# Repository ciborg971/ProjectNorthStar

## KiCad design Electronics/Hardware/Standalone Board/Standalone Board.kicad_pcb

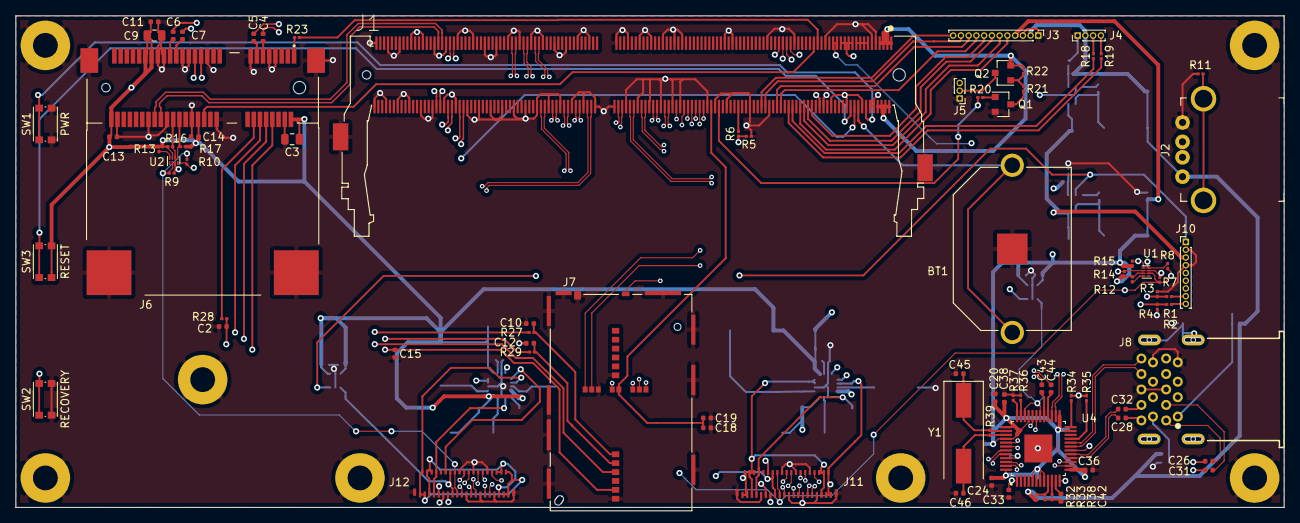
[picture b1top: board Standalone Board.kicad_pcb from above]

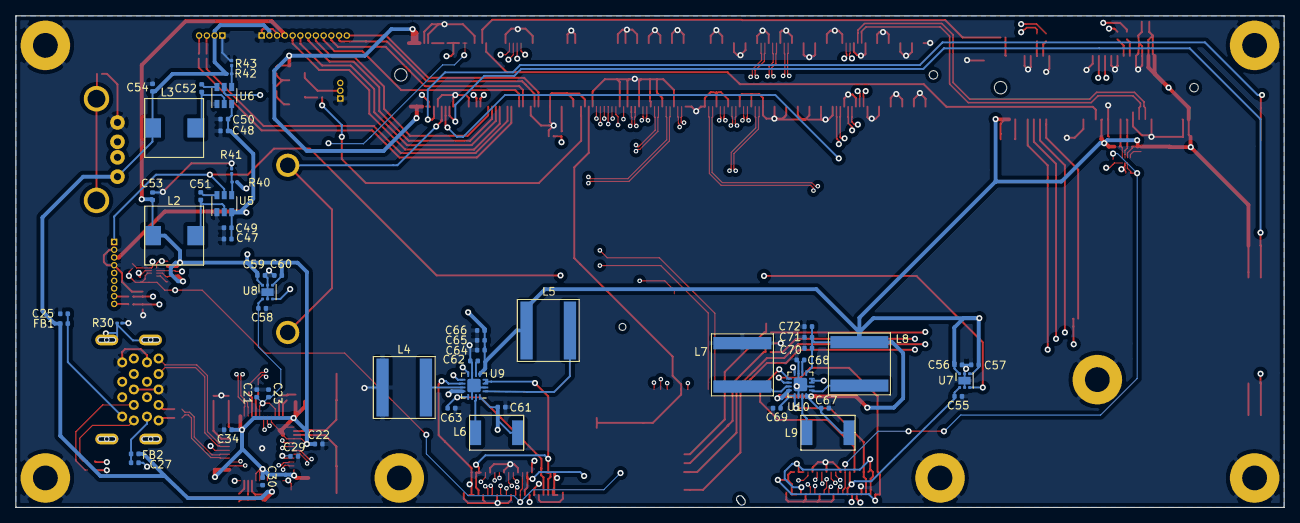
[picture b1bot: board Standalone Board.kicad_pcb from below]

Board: 4 copper layers, 163.8 x 63.5 mm, 146 parts (55 on the bottom side), 162 nets.

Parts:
BT1: BK-913; BAT_BK-913
C2, C10, C12: 3.3pF-50V; C_0402_1005Metric
C3, C9: 22uF 10V; C_0805_2012Metric
C4, C5, C6, C7, C22, C23, C24, C25, C26, C27, C28, C29, C30, C31, C32, C33, C34, C36, C38, C43, C44, C49, C50, C51, C52, C57, C60, C61, C62, C67, C68: 0.1uF; C_0402_1005Metric
C11, C13, C14, C19: 0.1uF 16V; C_0402_1005Metric
C15, C18: 1uF 6.3V; C_0402_1005Metric
C20, C42: 1uF; C_0402_1005Metric
C21, C47, C48, C55, C58, C63, C64, C65, C66, C69, C70, C71, C72: 10uF; C_0402_1005Metric
C45, C46: 30pF; C_0402_1005Metric
C53, C54: 22uF; C_0402_1005Metric
C56, C59: 2.2uF; C_0402_1005Metric
FB1, FB2: 220 @ 100mhz; L_0402_1005Metric
H1, H2, H3, H4, H5, H6: Mounting; MountingHole_3.2mm_M3_Pad
H7: 3.2Mounting; MountingHole_3.2mm_M3_Pad
J1: 2309411-2; TE_2309411-2
J2: USB_A; USB_A_Female_UE27AC54100
J3: GPIO; PinHeader_1x12_P1.00mm_Vertical
J4: DBG_UART1; PinHeader_1x04_P1.00mm_Vertical
J5: FAN1; PinHeader_1x03_P1.00mm_Vertical
J6: 2041119-1; TE_2041119-1
J7: 2290741-1; TE_2290741-1
J8: USB1100-XX-X_REVC; GCT_USB1100-XX-X_REVC
J10: PWR_IN; PinHeader_1x09_P1.00mm_Vertical
J11: FH35C-39S-0.3SHW(50) Left; FH35C-39S-0.3SHW(50)
J12: FH35C-39S-0.3SHW(50) Right; FH35C-39S-0.3SHW(50)
L2: 2.2uH 11mOhm; DRA74
L3: 3.3uH 17.7mOhm; DRA74
L4, L5, L7, L8: 4.7uH; NRS8040T4R7NJGJ
L6, L9: 10uH; SDR0703
Q1: MMBT3904; SOT-23
Q2: AO3415A; SOT-23
R1, R2, R6, R7, R8, R9, R10, R14, R15, R16, R17, R20, R21, R22, R41, R43: 10K; R_0201_0603Metric
R3, R4, R23: 100K; R_0201_0603Metric
R5: 15K; R_0201_0603Metric
R11, R30, R39: 1M; R_0201_0603Metric
R12, R13: 200K; R_0201_0603Metric
R18, R19, R27, R28, R29: 33R; R_0201_0603Metric
R32: 90.9K 1%; R_0201_0603Metric
R33: 10K 1%; R_0201_0603Metric
R34: 9.53K 1%; R_0201_0603Metric
R35, R36, R37: 4.7K; R_0201_0603Metric
R38: 1K; R_0201_0603Metric
R40: 33.2K; R_0201_0603Metric
R42: 54.9K; R_0201_0603Metric
SW1: PWR; SW_Push_1P1T_NO_CK_KMR2
SW2: RECOVERY; SW_Push_1P1T_NO_CK_KMR2
SW3: RESET; SW_Push_1P1T_NO_CK_KMR2
U1, U2: PCA9306; X2SON-8_1.4x1mm_P0.35mm
U4: TUSB8020BIPHP; QFP50P900X900X120-49N
U5, U6: TPS565208; SOT-23-6
U7: TPS7A11; WSON-6-1EP_2x2mm_P0.65mm_EP1x1.6mm
U8: TPS7A1111; WSON-6-1EP_2x2mm_P0.65mm_EP1x1.6mm
U9, U10: TPS65632; WQFN-16-1EP_3x3mm_P0.5mm_EP1.75x1.75mm
Y1: 24mhz; Crystal_SMD_HC49-SD

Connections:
+3V3: C3.1, C9.1, C11.1, C13.1, C14.1, C20.1, C22.1, C24.1, C30.1, C34.1, C36.1, C38.1, C53.1, C56.2, C57.1, C59.2, C60.1, C61.1, C64.1, C65.1, C66.1, C67.1, C70.1, C71.1, C72.1, J3.4, J6.2, J6.24, J6.39, J6.41, J6.52, L2.2, L5.1, L6.1, L8.1, L9.1, R12.1, R13.1, R14.1, R15.2, R16.1, R17.2, R40.1, SW3.2, U1.7, U2.7, U4.5, U4.7, U4.8, U4.13, U4.23, U4.25, U4.33, U4.37, U4.40, U4.48, U7.4, U7.6, U8.4, U8.6, U9.5, U9.12, U9.16, U10.5, U10.12, U10.16
+5V: C54.1, FB1.1, FB2.1, J2.1, J3.2, J4.2, L3.2, R32.2, R42.1
+12V: J1.1, J1.2, J1.3, J1.4, J1.5, J1.6, J1.7, J1.8, J10.5, Q2.2, R22.1
+BATT: C47.1, C48.1, C49.1, C50.1, J10.3, U5.3, U6.3
/1V1: C21.1, C23.1, C29.1, C33.1, C58.2, U4.1, U4.12, U4.18, U4.30, U4.34, U4.45, U8.1
/1V8: J1.29, J1.31, J11.23, J11.24, J12.23, J12.24, R7.1, R8.2, R9.1, R10.2, U1.2, U2.2
/3V0: C55.2, J11.25, J11.26, J12.25, J12.26, U7.1
/DISPLAY/AVDD_EN_R: J12.29, U10.8
/DISPLAY/AVDD_L: C63.1, J11.32, J11.33, U9.13
/DISPLAY/AVDD_L_EN: J11.29, U9.8
/DISPLAY/AVDD_R: C69.1, J12.32, J12.33, U10.13
/DISPLAY/OVDD_L: J11.4, J11.5, J11.6, J11.34, J11.35, J11.36, U9.3, U9.4
/DISPLAY/OVDD_R: J12.4, J12.5, J12.6, J12.34, J12.35, J12.36, U10.3, U10.4
/DISPLAY/OVSS_L: J11.1, J11.2, J11.3, J11.37, J11.38, J11.39, U9.10
/DISPLAY/OVSS_R: J12.1, J12.2, J12.3, J12.37, J12.38, J12.39, U10.10
/DISPLAY/RESET: J11.27, J12.27, R5.2, R6.1
/DISPLAY/SWIRE_L: J11.28, U9.9
/DISPLAY/SWIRE_R: J12.28, U10.9
/DISP_RST: J1.80, R6.2
/EN3V3: J1.21, J1.23, J1.25, J1.27, J10.1, U5.5, U6.5, U7.3, U8.3
/GPIO1_A1: J1.36, R1.1, R3.2
/GPIO1_A3: J1.38, R2.1, R4.2
/I2C_SCL_MPCIE: J6.32, R16.2, U2.6
/I2C_SCL_MPCIE_1.8V: J1.59, R9.2, U2.3
/I2C_SCL_PWR: J10.7, R14.2, U1.6
/I2C_SCL_PWR_1.8V: J1.53, R7.2, U1.3
/I2C_SDA_MPCIE: J6.30, R17.1, U2.5
/I2C_SDA_MPCIE_1.8V: J1.57, R10.1, U2.4
/I2C_SDA_PWR: J10.6, R15.1, U1.5
/I2C_SDA_PWR__1.8V: J1.55, R8.1, U1.4
/MIPI_TX0_CLK_N: J1.160, J12.14
/MIPI_TX0_CLK_P: J1.162, J12.15
/MIPI_TX0_D0_N: J1.172, J12.11
/MIPI_TX0_D0_P: J1.174, J12.12
/MIPI_TX0_D1_N: J1.166, J12.17
/MIPI_TX0_D1_P: J1.168, J12.18
/MIPI_TX0_D2_N: J1.154, J12.8
/MIPI_TX0_D2_P: J1.156, J12.9
/MIPI_TX0_D3_N: J1.148, J12.20
/MIPI_TX0_D3_P: J1.150, J12.21
/MIPI_TX1_CLK_N: J1.128, J11.14
/MIPI_TX1_CLK_P: J1.130, J11.15
/MIPI_TX1_D0_N: J1.116, J11.11
/MIPI_TX1_D0_P: J1.118, J11.12
/MIPI_TX1_D1_N: J1.122, J11.17
/MIPI_TX1_D1_P: J1.124, J11.18
/MIPI_TX1_D2_N: J1.134, J11.8
/MIPI_TX1_D2_P: J1.136, J11.9
/MIPI_TX1_D3_N: J1.140, J11.20
/MIPI_TX1_D3_P: J1.142, J11.21
/MPCIE SIM SDCARD/USIM_CLK: C10.1, J7.C3_1, R27.2
/MPCIE SIM SDCARD/USIM_DATA: C12.1, J7.C7_1, R29.2
/MPCIE SIM SDCARD/USIM_RST: C2.1, J7.C2_1, R28.2
/MPCIE SIM SDCARD/USIM_VCC: C15.1, J6.8, J7.C1_1
/PCIE_CLK_N: C5.2, J1.226
/PCIE_CLK_P: C4.2, J1.228
/PCIE_RST_N: J1.41, J6.22
/PCIE_RX0_N: J1.214, J6.25
/PCIE_RX0_P: J1.216, J6.23
/PCIE_TX0_N: C7.2, J1.220
/PCIE_TX0_P: C6.2, J1.222
/PCIE_WAKE_N: J1.39, R23.2
/POWER/INT_A: J10.8, R1.2
/POWER/INT_B: J10.9, R2.2
/SDMMC_CLK: J1.112, J7.P5
/SDMMC_CMD: J1.106, J7.P3
/SDMMC_D0: J1.98, J7.P7
/SDMMC_D1: J1.100, J7.P8
/SDMMC_D2: J1.102, J7.P1
/SDMMC_D3: J1.104, J7.P2
/SDMMC_DET_L: J1.108, J7.SW/CD
/USB3.0_D_N: J1.177, U4.27
/USB3.0_D_P: J1.175, U4.26
/USB3.0_RX1_N: J1.189, U4.31
/USB3.0_RX1_P: J1.187, U4.32
/USB3.0_TX1_N: C44.2, J1.183
/USB3.0_TX1_P: C43.2, J1.181
/USB 3.0 Hub/USB0_D_N: J8.2, U4.41
/USB 3.0 Hub/USB0_D_P: J8.3, U4.42
/USB 3.0 Hub/USB0_SSRX_N: J8.5, U4.47
/USB 3.0 Hub/USB0_SSRX_P: J8.6, U4.46
/USB 3.0 Hub/USB0_SSTX_N: C31.2, U4.43
/USB 3.0 Hub/USB0_SSTX_P: C26.2, U4.44
/USB 3.0 Hub/USB1_D_N: J8.11, U4.15
/USB 3.0 Hub/USB1_D_P: J8.12, U4.14
/USB 3.0 Hub/USB1_SSRX_N: J8.14, U4.20
/USB 3.0 Hub/USB1_SSRX_P: J8.15, U4.19
/USB 3.0 Hub/USB1_SSTX_N: C32.2, U4.17
/USB 3.0 Hub/USB1_SSTX_P: C28.2, U4.16
/USB_HOST0_D_N: J1.221, J2.2
/USB_HOST0_D_P: J1.219, J2.3
/USB_HOST1_D_N: J1.227, J6.36
/USB_HOST1_D_P: J1.225, J6.38
/VCC3V0_SD: C18.1, C19.1, J1.94, J7.P4
/som/GPIO1_C2: J1.42, J3.8
/som/GPIO1_C6: J1.44, J3.7
/som/GPIO1_C7: J1.46, J3.6
/som/GPIO1_D0: J1.48, J3.5
/som/GPIO4_C0_I2C3_SDA: J1.68, J3.12
/som/GPIO4_C1_I2C3_SCL: J1.66, J3.11
/som/GPIO4_C6_PWM1: J1.90, R20.1
/som/PWR_KEY: J1.14, SW1.1
/som/RECOVERY: J1.20, SW2.1
/som/RESET_IN_H: J1.22, SW3.1
/som/RTC_BATT_IN: BT1.S1, BT1.S2, J1.18
/som/UART2DBG_RX: J1.54, R19.2
/som/UART2DBG_TX: J1.52, R18.2
/som/UART4_RX: J1.60, J3.10
/som/UART4_TX: J1.58, J3.9
/som/VCC5V0_SYS: J1.13, J1.15, J1.17, J1.19
GND: BT1.1, C2.2, C3.2, C9.2, C10.2, C11.2, C12.2, C13.2, C14.2, C15.2, C18.2, C19.2, C20.2, C21.2, C22.2, C23.2, C24.2, C25.1, C27.1, C29.2, C30.2, C33.2, C34.2, C36.2, C38.2, C42.2, C45.1, C46.1, C47.2, C48.2, C49.2, C50.2, C53.2, C54.2, C55.1, C56.1, C57.2, C58.1, C59.1, C60.2, C61.2, C62.2, C63.2, C64.2, C65.2, C66.2, C67.2, C68.2, C69.2, C70.2, C71.2, C72.2, H1.1, H2.1, H3.1, H4.1, H5.1, H6.1, H7.1, J1.9, J1.10, J1.11, J1.12, J1.16, J1.24, J1.32, J1.35, J1.51, J1.64, J1.65, J1.74, J1.83, J1.86, J1.87, J1.92, J1.96, J1.109, J1.110, J1.113, J1.114, J1.119, J1.120, J1.125, J1.126, J1.131, J1.132, J1.137, J1.138, J1.143, J1.144, J1.146, J1.149, J1.152, J1.155, J1.158, J1.161, J1.164, J1.167, J1.170, J1.173, J1.176, J1.179, J1.182, J1.185, J1.188, J1.191, J1.194, J1.197, J1.200, J1.203, J1.206, J1.209, J1.212, J1.217, J1.218, J1.223, J1.224, J1.229, J1.230, J1.235, J1.236, J1.241, J1.242, J1.247, J1.248, J1.253, J1.254, J1.259, J1.260, J1.S1, J1.S2, J2.4, J3.1, J3.3, J4.1, J5.1, J6.4, J6.7, J6.9, J6.15, J6.18, J6.21, J6.26, J6.27, J6.29, J6.34, J6.35, J6.37, J6.40, J6.43, J6.50, J6.S1, J6.S2, J6.S3, J6.S4, J7.C5_1, J7.C5_2, J7.GND1, J7.GND2, J7.GND3, J7.GND4, J7.GND5, J7.GND6, J7.GND7, J7.GND8, J7.GND9, J7.P6, J7.SW/GND, J8.4, J8.7, J8.13, J8.16, J10.2, J10.4, J11.7, J11.10, J11.13, J11.16, J11.19, J11.22, J11.31, J11.40, J12.7, J12.10, J12.13, J12.16, J12.19, J12.22, J12.31, J12.40, L4.1, L7.1, Q1.2, R3.1, R4.1, R5.1, R11.2, R30.2, R33.2, R34.2, R35.2, R36.2, R37.2, R38.2, R41.2, R43.2, SW1.2, SW2.2, U4.49, U5.1, U6.1, U7.2, U7.5, U7.7, U8.2, U8.5, U8.7, U9.2, U9.7, U9.14, U9.17, U10.2, U10.7, U10.14, U10.17
unnamed: C4.1, J6.11
unnamed: C5.1, J6.13
unnamed: C6.1, J6.33
unnamed: C7.1, J6.31
unnamed: C25.2, FB1.2, J8.1
unnamed: C26.1, J8.9
unnamed: C27.2, FB2.2, J8.10
unnamed: C28.1, J8.18
unnamed: C31.1, J8.8
unnamed: C32.1, J8.17
unnamed: C42.1, U4.11
unnamed: C43.1, U4.29
unnamed: C44.1, U4.28
unnamed: C45.2, R39.1, U4.38, Y1.1
unnamed: C46.2, R39.2, U4.39, Y1.2
unnamed: C51.1, L2.1, U5.2
unnamed: C51.2, U5.6
unnamed: C52.1, L3.1, U6.2
unnamed: C52.2, U6.6
unnamed: C62.1, U9.6
unnamed: C68.1, U10.6
unnamed: J2.SH, R11.1
unnamed: J4.3, R18.1
unnamed: J4.4, R19.1
unnamed: J5.2, Q2.3
unnamed: J6.1, R23.1
unnamed: J6.10, R29.1
unnamed: J6.12, R27.1
unnamed: J6.14, R28.1
unnamed: J6.17, J6.19, J6.45, J6.47, J6.49, J6.51
unnamed: J6.6, J6.28, J6.48
unnamed: J8.19, J8.20, J8.21, J8.22, R30.1
unnamed: L4.2, U9.11
unnamed: L5.2, U9.1
unnamed: L6.2, U9.15
unnamed: L7.2, U10.11
unnamed: L8.2, U10.1
unnamed: L9.2, U10.15
unnamed: Q1.1, R20.2
unnamed: Q1.3, R21.2
unnamed: Q2.1, R21.1, R22.2
unnamed: R12.2, U1.8
unnamed: R13.2, U2.8
unnamed: R32.1, R33.1, U4.9
unnamed: R34.1, U4.24
unnamed: R35.1, U4.21
unnamed: R36.1, U4.35
unnamed: R37.1, U4.36
unnamed: R38.1, U4.10
unnamed: R40.2, R41.1, U5.4
unnamed: R42.2, R43.1, U6.4

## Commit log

2019-12-11 Add schematic for som, led driver and mpcie bay. Add doc for boe amoled display
2019-12-11 Add debug uart, gps uart, fan control and sdcard
2019-12-12 Add rtc, pcie + mipi dsi high level connection, usb 2.0, usb 3.0 and remove audio section
2019-12-13 Fix all i2c voltage, add power/reset/recovery button, Mipi dsi hig level, add 3.0/3.3/5/1.1 volt power rail
2019-12-13 Add Readme for standalone board
2019-12-23 Everything is routed, TODO : lenghtmatching + impedance matching + cleaning
2020-03-01 Fix silkscreen
